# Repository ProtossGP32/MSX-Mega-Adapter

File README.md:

# MSX Mega Adapter
This is a quick and easy version of the [JoyMega](https://www.msx.org/wiki/JoyMega) for the MSX-line of computers, I believe they were originally a design by [FRS](http://frs.badcoffee.info/hardware/joymega-en.html) as he did a very detailed writeup of its development over various revisions. Instead of going by his latest revisions as a starting point, this was instead created to be easily built using the kind of parts I already had laying around the house (mostly from ebay and AliExpress). Functionally it remains the same, just easier to build for us novices to all things that have yet to be soldered together.

# 1> Building the adapter
Building the unit assumes you have at least minor experience when it comes to soldering things together, mainly being able to figure out which parts to not touch and how not to set your table on fire. What I recommended is that you at least have a soldering station with adjustable temperature when getting started, 60/40 solder tin if that stuff is still available where you live.

With the equipment sorted, let's take a step back and focus on what's important in this day and age - shopping. Head on over to the [BOM](#3-bom)-section for some basuc information on what you need, with sites such as ebay, AliExpress, Wish etc you'll mostly need to treat these as a starting point for what to put into the search engine. By checking out the gallery images, you should be able to discern which you'll need. Considering the delivery times to expect from China, I usually order one of each when in doubt - it should be cheap enough and I'll find a use for them sooner or later.

## 1.1> Soldering it together
The construction of this unit should be straight-forward, observe the direction of the diodes and solder those in - matching the stripes on the board to the ones on the diodes themselves. Then do the resistors and capacitors, followed by the DIP sockets - taking care to match the silkscreen indication for where the first pin should go (the indent). Skipping sockets is strictly not recommended, unless you happen to know that the chips came from reliable sources.

Save the large DB9 connectors for last, mainly because it'll be a bit cumbersome with those things in the way. When ready, ensure that you use the male connector on the side marked Sega Mega Drive and the female on on the MSX-side.

In the picture I've chosen to just unscrew and remove the metal shielding, I find that on some vintage systems the ports are very tight to the extent that it might split the plastic (plastic might have gone brittle over the years) - if it feels loose when plugged into the machine then you'll need to have the shielding in place. One problem is that the mounting screws holding the machine will get in the way, so we'll need to figure out something else here. One option is to simply superglue the shield into place, using solder to fill the hole where the screw would usually go or just to find some M3 flat head screws and use those instead.

For your final trick, insert the single IC into the socket - matching up the indent in the socket and silkscreen markings with the indent on the actual IC. Inserting it the wrong way will more than likely require purchasing another one. When satisfied with the results, go forward and test it on your least favourite MSX-computer (just to be safe). As with all things that includes active circuitry, never plug or unplug them while the computer is powered on.

## 1.2> Testing it out
This is the step where things start getting complicated, mostly because there are so many titles that don't really support more than a single button. Testing out that specific button should be easy then, but we'll need to test out the rest of them as well.

Thankfully, there is a software package available so that you can do this - [HIDTEST](https://msxhub.com/HIDTEST). You need a disk drive to be able to load this up, I used an external Gotek drive with mine to copy it over to a physical floppy (needed [MSX Disk-Manager](https://msxhub.com/HIDTEST) to get the files into a blank disk image first). If all goes well, it should automatically detect that you've connected a Sega Mega Drive controller and you test each button separately (all of them should be available to you).

# 2> Schematic
The supplied KiCad files should be sufficient as both a schematic and as a  starting point for ordering PCBs (basically you could just zip the contents of the export folder and upload that on a fabrication site), the schematic is also available in [PDF-format](export/MSX%20Mega%20Adapter.pdf) and this is what you'll need to print and work your way through this things don't work as expected after assembly.

# 3> BOM
Most parts should be easy to get a hold of from your favourite local electronic component shop, but given that I don't have access to such shops where I live so everything was based on whatever I could get cheapest from eBay/AliExpress. By looking around you could probably find a seller with free shipping, but plan well in advance as 3-4 weeks delivery times is to be considered on the *faster* side of things.

| Reference    | Item                                  | Count |
| ------------ | ------------------------------------- | ----- |
| PCB          | Fabricate using Gerber files          |     1 |
| C1           | 100nF ceramic capacitor (5mm)         |     1 |
| D1,D2 *      | 1n5711 diode (DO-35)                  |     2 |
| J1           | Female DB9 right-angle connector      |     1 |
| J2           | Male DB9 right-angle connector        |     1 |
| U1           | 74HCT04 (DIP-14)                      |     1 |

*) These can be substituted with BAT-85 diodes instead. Not tested, but you could also try out standard 1n4148 diodes instead as those are often used with adapters of this type.

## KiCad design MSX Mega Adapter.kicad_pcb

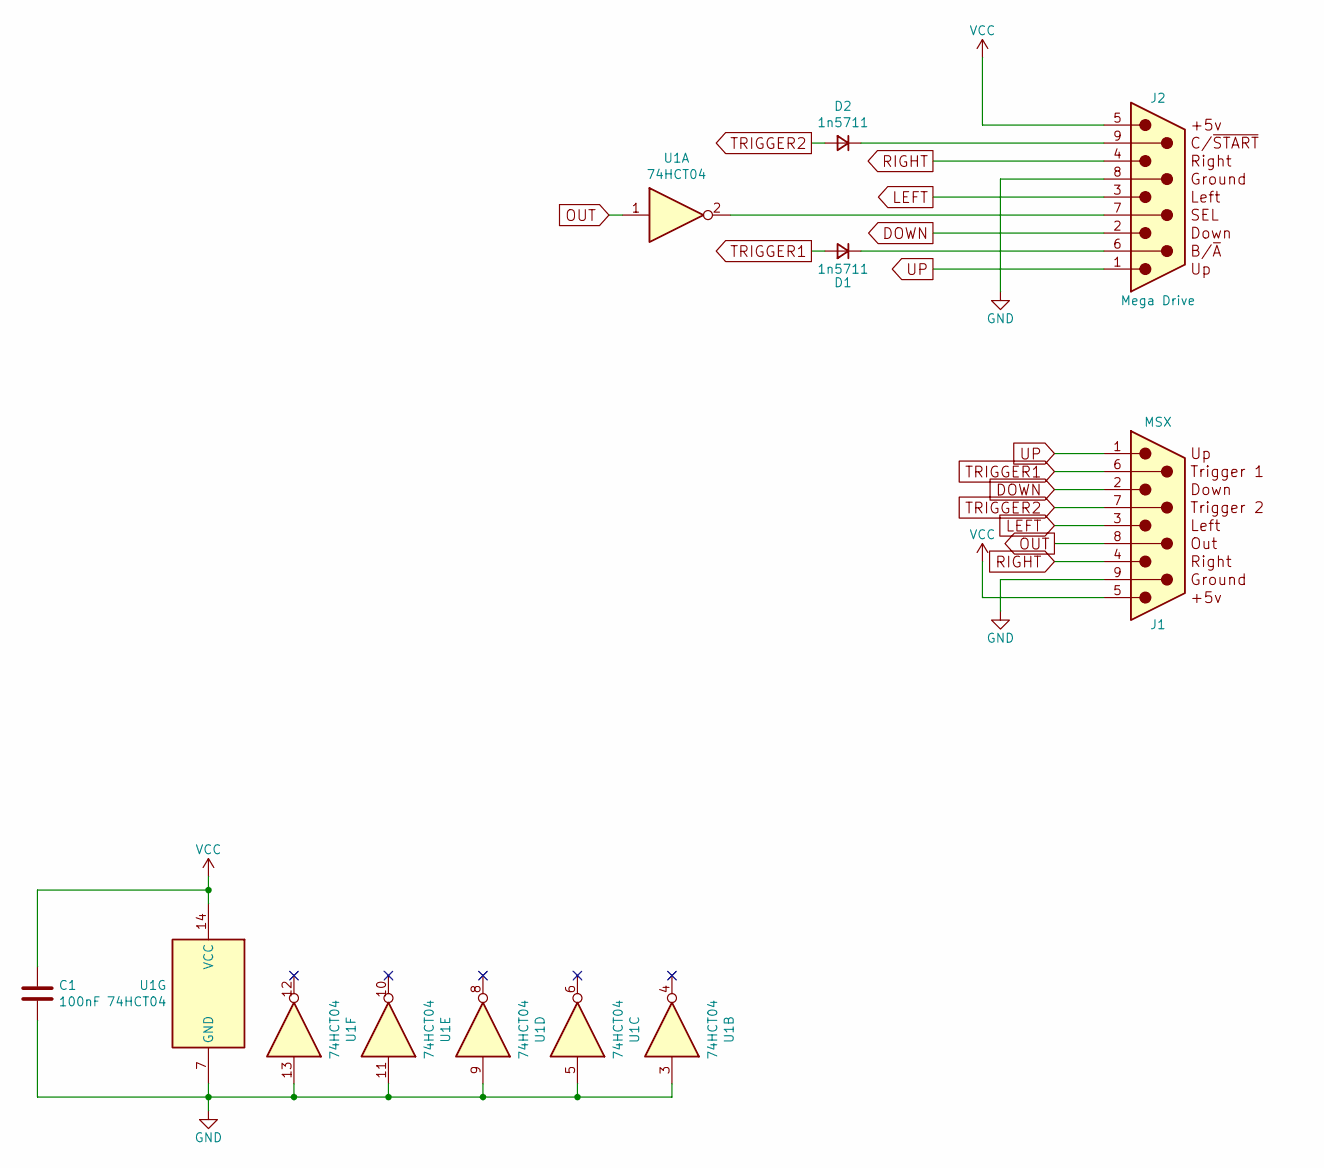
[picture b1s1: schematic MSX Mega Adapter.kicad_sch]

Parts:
C1: 100nF; C_Disc_D4.7mm_W2.5mm_P5.00mm
D1, D2: 1n5711; D_DO-35_SOD27_P7.62mm_Horizontal
J1: MSX; DSUB-9_Female_Horizontal_P2.77x2.84mm_EdgePinOffset7.70mm_H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
J2: Mega Drive; DSUB-9_Male_Horizontal_P2.77x2.84mm_EdgePinOffset7.70mm_Hou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
U1: 74HCT04; DIP-14_W7.62mm_Socket_LongPads

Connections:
DOWN: J1.2, J2.2
GND: C1.2, J1.9 (GND), J2.8 (GND), U1.3, U1.5, U1.7 (GND), U1.9, U1.11, U1.13
LEFT: J1.3, J2.3
unnamed: D1.1 (K), J2.6
unnamed: D2.1 (K), J2.9
unnamed: J2.7, U1.2
OUT: J1.8 (OUT), U1.1
RIGHT: J1.4, J2.4
TRIGGER1: D1.2 (A), J1.6
TRIGGER2: D2.2 (A), J1.7
UP: J1.1, J2.1
VCC: C1.1, J1.5 (VCC), J2.5 (VCC), U1.14 (VCC)

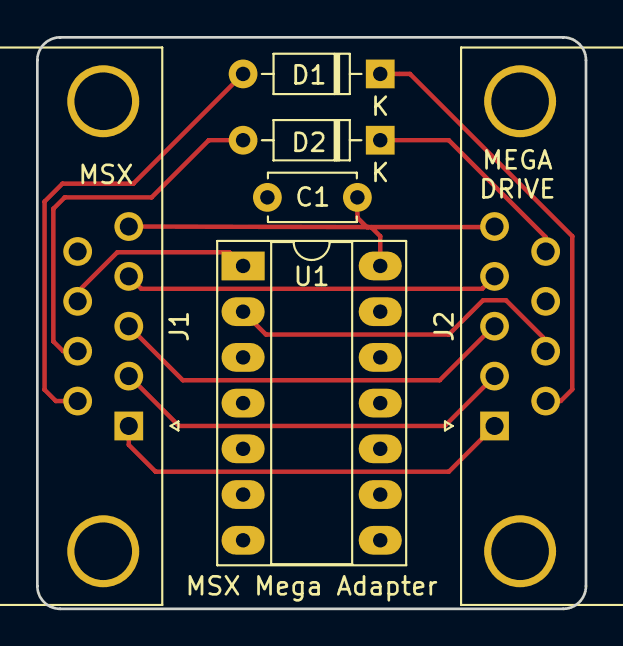
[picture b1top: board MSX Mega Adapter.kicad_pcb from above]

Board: 2 copper layers, 30.5 x 31.8 mm, 6 parts (0 on the bottom side), 12 nets.

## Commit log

2022-11-26 UPD: Updated README.md with relative links to the images
2022-11-27 UPD: Updated KiCAD project to v6.0 - Also changed 3D objects references to default KiCAD6 paths, so no extra modules are required
2022-11-27 UPD: Updated KiCAD cache and library table files
2022-11-27 NEW: Added WIP version of MSX Mega Adapter case
2022-11-27 FIX: Fixed corrupted hierarchy in main part
2022-11-30 UPD: Several changes: - Fixed M2.5 holes and poles - Added MSX and MD logos on both top and bottom pieces - Added external fillets
2023-04-03 feat: designed wired case - MSX-side screw poles must be redimensioned as the DB9 female is out
2023-11-12 feat: new AAMSX wired case

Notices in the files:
MSX Mega Adapter.kicad_pcb:
Licensed under
CERN OHL v.1.2
